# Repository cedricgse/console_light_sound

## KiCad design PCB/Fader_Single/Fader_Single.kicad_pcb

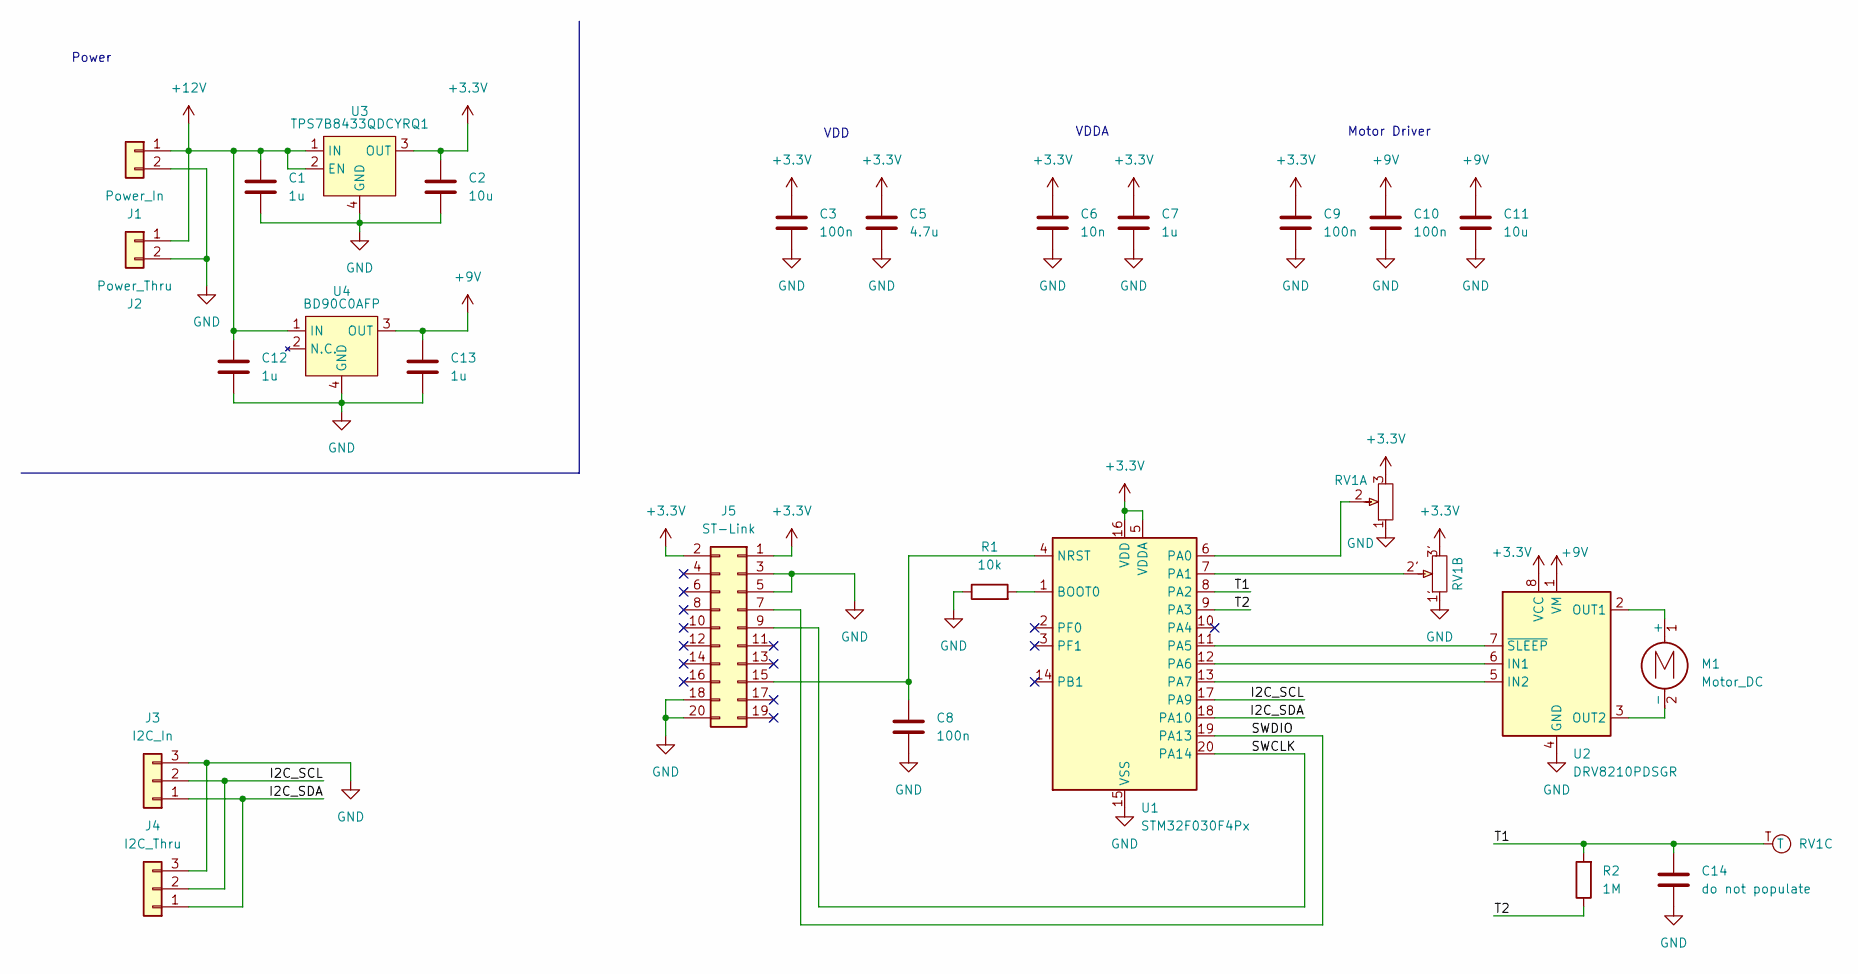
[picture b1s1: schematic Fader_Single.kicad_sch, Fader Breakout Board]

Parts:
C1, C7, C12, C13: 1u; C_0805_2012Metric
C2, C11: 10u; C_0805_2012Metric
C3, C8, C9, C10: 100n; C_0805_2012Metric
C5: 4.7u; C_0805_2012Metric
C6: 10n; C_0805_2012Metric
C14: do not populate; C_0805_2012Metric
J1: Power_In; PinHeader_1x02_P2.54mm_Vertical
J2: Power_Thru; PinHeader_1x02_P2.54mm_Vertical
J3: I2C_In; PinHeader_1x03_P2.54mm_Vertical
J4: I2C_Thru; PinHeader_1x03_P2.54mm_Vertical
J5: ST-Link; PinHeader_2x10_P2.54mm_Vertical
M1: Motor_DC; SolderWire-0.5sqmm_1x02_P4.8mm_D0.9mm_OD2.3mm
R1: 10k; R_0805_2012Metric
R2: 1M; R_0805_2012Metric
RV1: Motorfader
U1: STM32F030F4Px; TSSOP-20_4.4x6.5mm_P0.65mm
U2: DRV8210PDSGR; WSON-8-1EP_2x2mm_P0.5mm_EP0.9x1.6mm_ThermalVias
U3: TPS7B8433QDCYRQ1; SOT-223
U4: BD90C0AFP; TO-252-3_TabPin4

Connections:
+3.3V: C2.1, C3.1, C5.1, C6.1, C7.1, C9.1, J5.1, J5.2, RV1.3, RV1.3', U1.5 (VDDA), U1.16 (VDD), U2.8 (VCC), U3.3 (OUT)
+9V: C10.1, C11.1, C13.1, U2.1 (VM), U4.3 (OUT)
+12V: C1.1, C12.1, J1.1, J2.1, U3.1 (IN), U3.2 (EN), U4.1 (IN)
/I2C_SCL: J3.2, J4.2, U1.17 (PA9)
/I2C_SDA: J3.1, J4.1, U1.18 (PA10)
/SWCLK: J5.9, U1.20 (PA14)
/SWDIO: J5.7, U1.19 (PA13)
/T1: C14.1, R2.2, RV1.T, U1.8 (PA2)
/T2: R2.1, U1.9 (PA3)
GND: C1.2, C2.2, C3.2, C5.2, C6.2, C7.2, C8.2, C9.2, C10.2, C11.2, C12.2, C13.2, C14.2, J1.2, J2.2, J3.3, J4.3, J5.3, J5.5, J5.18, J5.20, R1.1, RV1.1, RV1.1', U1.15 (VSS), U2.4 (GND), U2.9 (GND), U3.4 (GND), U4.4 (GND)
unnamed: C8.1, J5.15, U1.4 (NRST)
unnamed: M1.1 (+), U2.2 (OUT1)
unnamed: M1.2 (-), U2.3 (OUT2)
unnamed: R1.2, U1.1 (BOOT0)
unnamed: RV1.2, U1.6 (PA0)
unnamed: RV1.2', U1.7 (PA1)
unnamed: U1.11 (PA5), U2.7 (~SLEEP)
unnamed: U1.12 (PA6), U2.6 (IN1)
unnamed: U1.13 (PA7), U2.5 (IN2)

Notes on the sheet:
VDDA
Power
Motor Driver
VDD

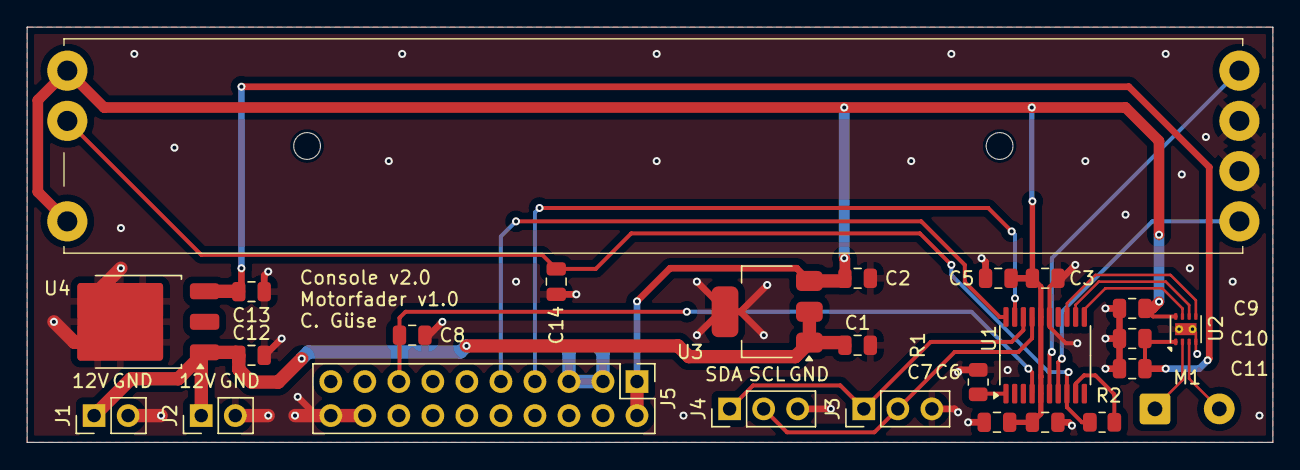
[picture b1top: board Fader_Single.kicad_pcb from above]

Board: 2 copper layers, 93.0 x 31.0 mm, 26 parts (0 on the bottom side), 19 nets.

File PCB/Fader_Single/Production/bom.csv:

Designator,Footprint,Quantity,Value,LCSC Part #
"C1, C12, C13, C7",0805,4,1u,
"C10, C3, C8, C9",0805,4,100n,
"C11, C2",0805,2,10u,
C14,0805,1,do not populate,
C5,0805,1,4.7u,
C6,0805,1,10n,
J1,PinHeader_1x02_P2.54mm_Vertical,1,Power_In,
J2,PinHeader_1x02_P2.54mm_Vertical,1,Power_Thru,
J3,PinHeader_1x03_P2.54mm_Vertical,1,I2C_In,
J4,PinHeader_1x03_P2.54mm_Vertical,1,I2C_Thru,
J5,PinHeader_2x10_P2.54mm_Vertical,1,ST-Link,
M1,SolderWire-0.5sqmm_1x02_P4.8mm_D0.9mm_OD2.3mm,1,Motor_DC,
R1,0805,1,10k,
R2,0805,1,1M,
RV1,Motorfader,1,~,
U1,TSSOP-20_4.4x6.5mm_P0.65mm,1,STM32F030F4Px,
U2,WSON-8-1EP_2x2mm_P0.5mm_EP0.9x1.6mm_ThermalVias,1,DRV8210PDSGR,
U3,SOT-223,1,~,
U4,TO-252-3_TabPin4,1,~,

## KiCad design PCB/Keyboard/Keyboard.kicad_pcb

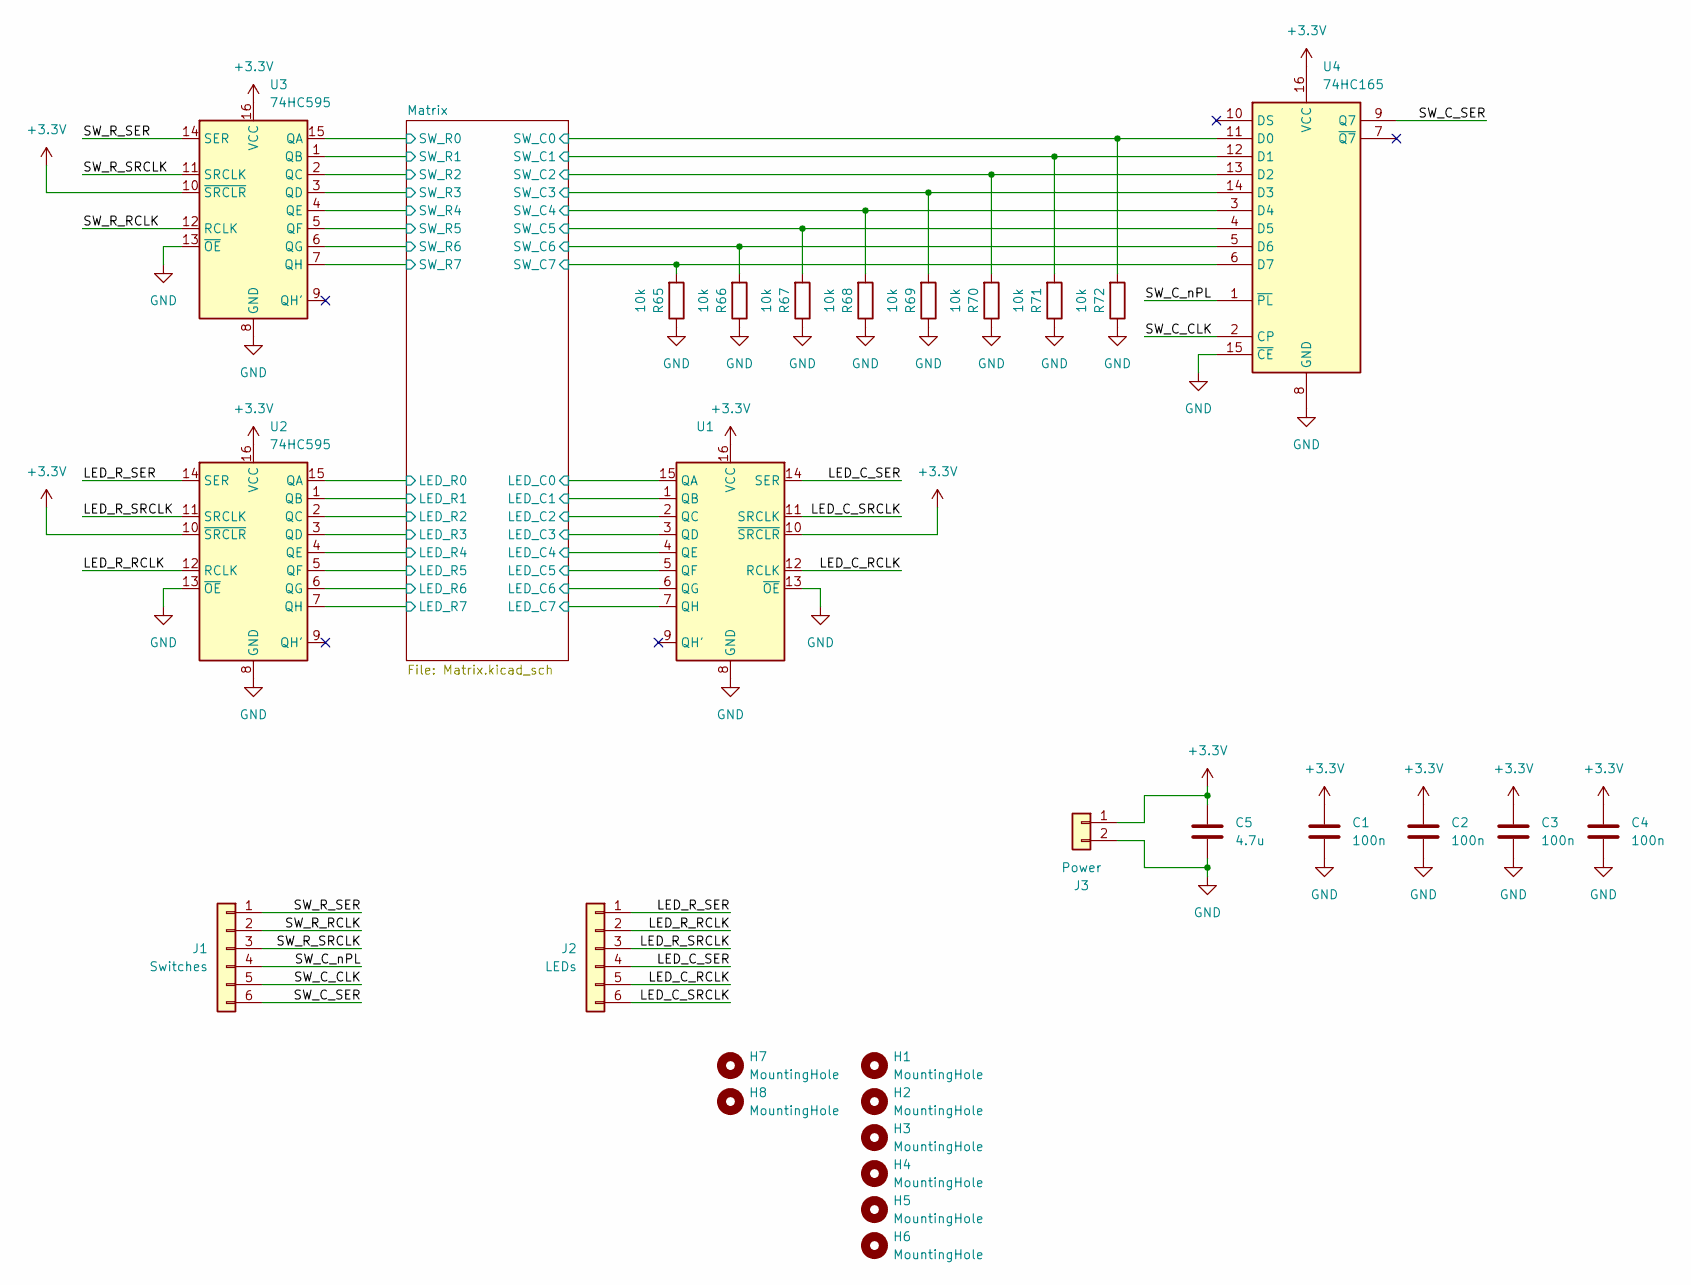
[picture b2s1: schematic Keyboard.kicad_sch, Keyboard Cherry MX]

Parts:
C1, C2, C3, C4: 100n; C_0805_2012Metric
C5: 4.7u; C_0805_2012Metric
H1, H2, H3, H4, H5, H6, H7, H8: MountingHole; MountingHole_3.2mm_M3
J1: Switches; PinHeader_1x06_P2.54mm_Vertical
J2: LEDs; PinHeader_1x06_P2.54mm_Vertical
J3: Power; PinHeader_1x02_P2.54mm_Vertical
R65, R66, R67, R68, R69, R70, R71, R72: 10k; R_0805_2012Metric
U1, U2, U3: 74HC595; SO-16_3.9x9.9mm_P1.27mm
U4: 74HC165; SO-16_3.9x9.9mm_P1.27mm

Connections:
+3.3V: C1.1, C2.1, C3.1, C4.1, C5.1, J3.1, U1.10 (~SRCLR), U1.16 (VCC), U2.10 (~SRCLR), U2.16 (VCC), U3.10 (~SRCLR), U3.16 (VCC), U4.16 (VCC)
/LED_C_RCLK: J2.5, U1.12 (RCLK)
/LED_C_SER: J2.4, U1.14 (SER)
/LED_C_SRCLK: J2.6, U1.11 (SRCLK)
/LED_R_RCLK: J2.2, U2.12 (RCLK)
/LED_R_SER: J2.1, U2.14 (SER)
/LED_R_SRCLK: J2.3, U2.11 (SRCLK)
/Matrix/LED_C0: U1.15 (QA); also elsewhere on the board
/Matrix/LED_C1: U1.1 (QB); also elsewhere on the board
/Matrix/LED_C2: U1.2 (QC); also elsewhere on the board
/Matrix/LED_C3: U1.3 (QD); also elsewhere on the board
/Matrix/LED_C4: U1.4 (QE); also elsewhere on the board
/Matrix/LED_C5: U1.5 (QF); also elsewhere on the board
/Matrix/LED_C6: U1.6 (QG); also elsewhere on the board
/Matrix/LED_C7: U1.7 (QH); also elsewhere on the board
/Matrix/LED_R0: U2.15 (QA); also elsewhere on the board
/Matrix/LED_R1: U2.1 (QB); also elsewhere on the board
/Matrix/LED_R2: U2.2 (QC); also elsewhere on the board
/Matrix/LED_R3: U2.3 (QD); also elsewhere on the board
/Matrix/LED_R4: U2.4 (QE); also elsewhere on the board
/Matrix/LED_R5: U2.5 (QF); also elsewhere on the board
/Matrix/LED_R6: U2.6 (QG); also elsewhere on the board
/Matrix/LED_R7: U2.7 (QH); also elsewhere on the board
/Matrix/SW_C0: R72.2, U4.11 (D0); also elsewhere on the board
/Matrix/SW_C1: R71.2, U4.12 (D1); also elsewhere on the board
/Matrix/SW_C2: R70.2, U4.13 (D2); also elsewhere on the board
/Matrix/SW_C3: R69.2, U4.14 (D3); also elsewhere on the board
/Matrix/SW_C4: R68.2, U4.3 (D4); also elsewhere on the board
/Matrix/SW_C5: R67.2, U4.4 (D5); also elsewhere on the board
/Matrix/SW_C6: R66.2, U4.5 (D6); also elsewhere on the board
/Matrix/SW_C7: R65.2, U4.6 (D7); also elsewhere on the board
/Matrix/SW_R0: U3.15 (QA); also elsewhere on the board
/Matrix/SW_R1: U3.1 (QB); also elsewhere on the board
/Matrix/SW_R2: U3.2 (QC); also elsewhere on the board
/Matrix/SW_R3: U3.3 (QD); also elsewhere on the board
/Matrix/SW_R4: U3.4 (QE); also elsewhere on the board
/Matrix/SW_R5: U3.5 (QF); also elsewhere on the board
/Matrix/SW_R6: U3.6 (QG); also elsewhere on the board
/Matrix/SW_R7: U3.7 (QH); also elsewhere on the board
/SW_C_CLK: J1.5, U4.2 (CP)
/SW_C_SER: J1.6, U4.9 (Q7)
/SW_C_nPL: J1.4, U4.1 (~PL)
/SW_R_RCLK: J1.2, U3.12 (RCLK)
/SW_R_SER: J1.1, U3.14 (SER)
/SW_R_SRCLK: J1.3, U3.11 (SRCLK)
GND: C1.2, C2.2, C3.2, C4.2, C5.2, J3.2, R65.1, R66.1, R67.1, R68.1, R69.1, R70.1, R71.1, R72.1, U1.8 (GND), U1.13 (~OE), U2.8 (GND), U2.13 (~OE), U3.8 (GND), U3.13 (~OE), U4.8 (GND), U4.15 (~CE)

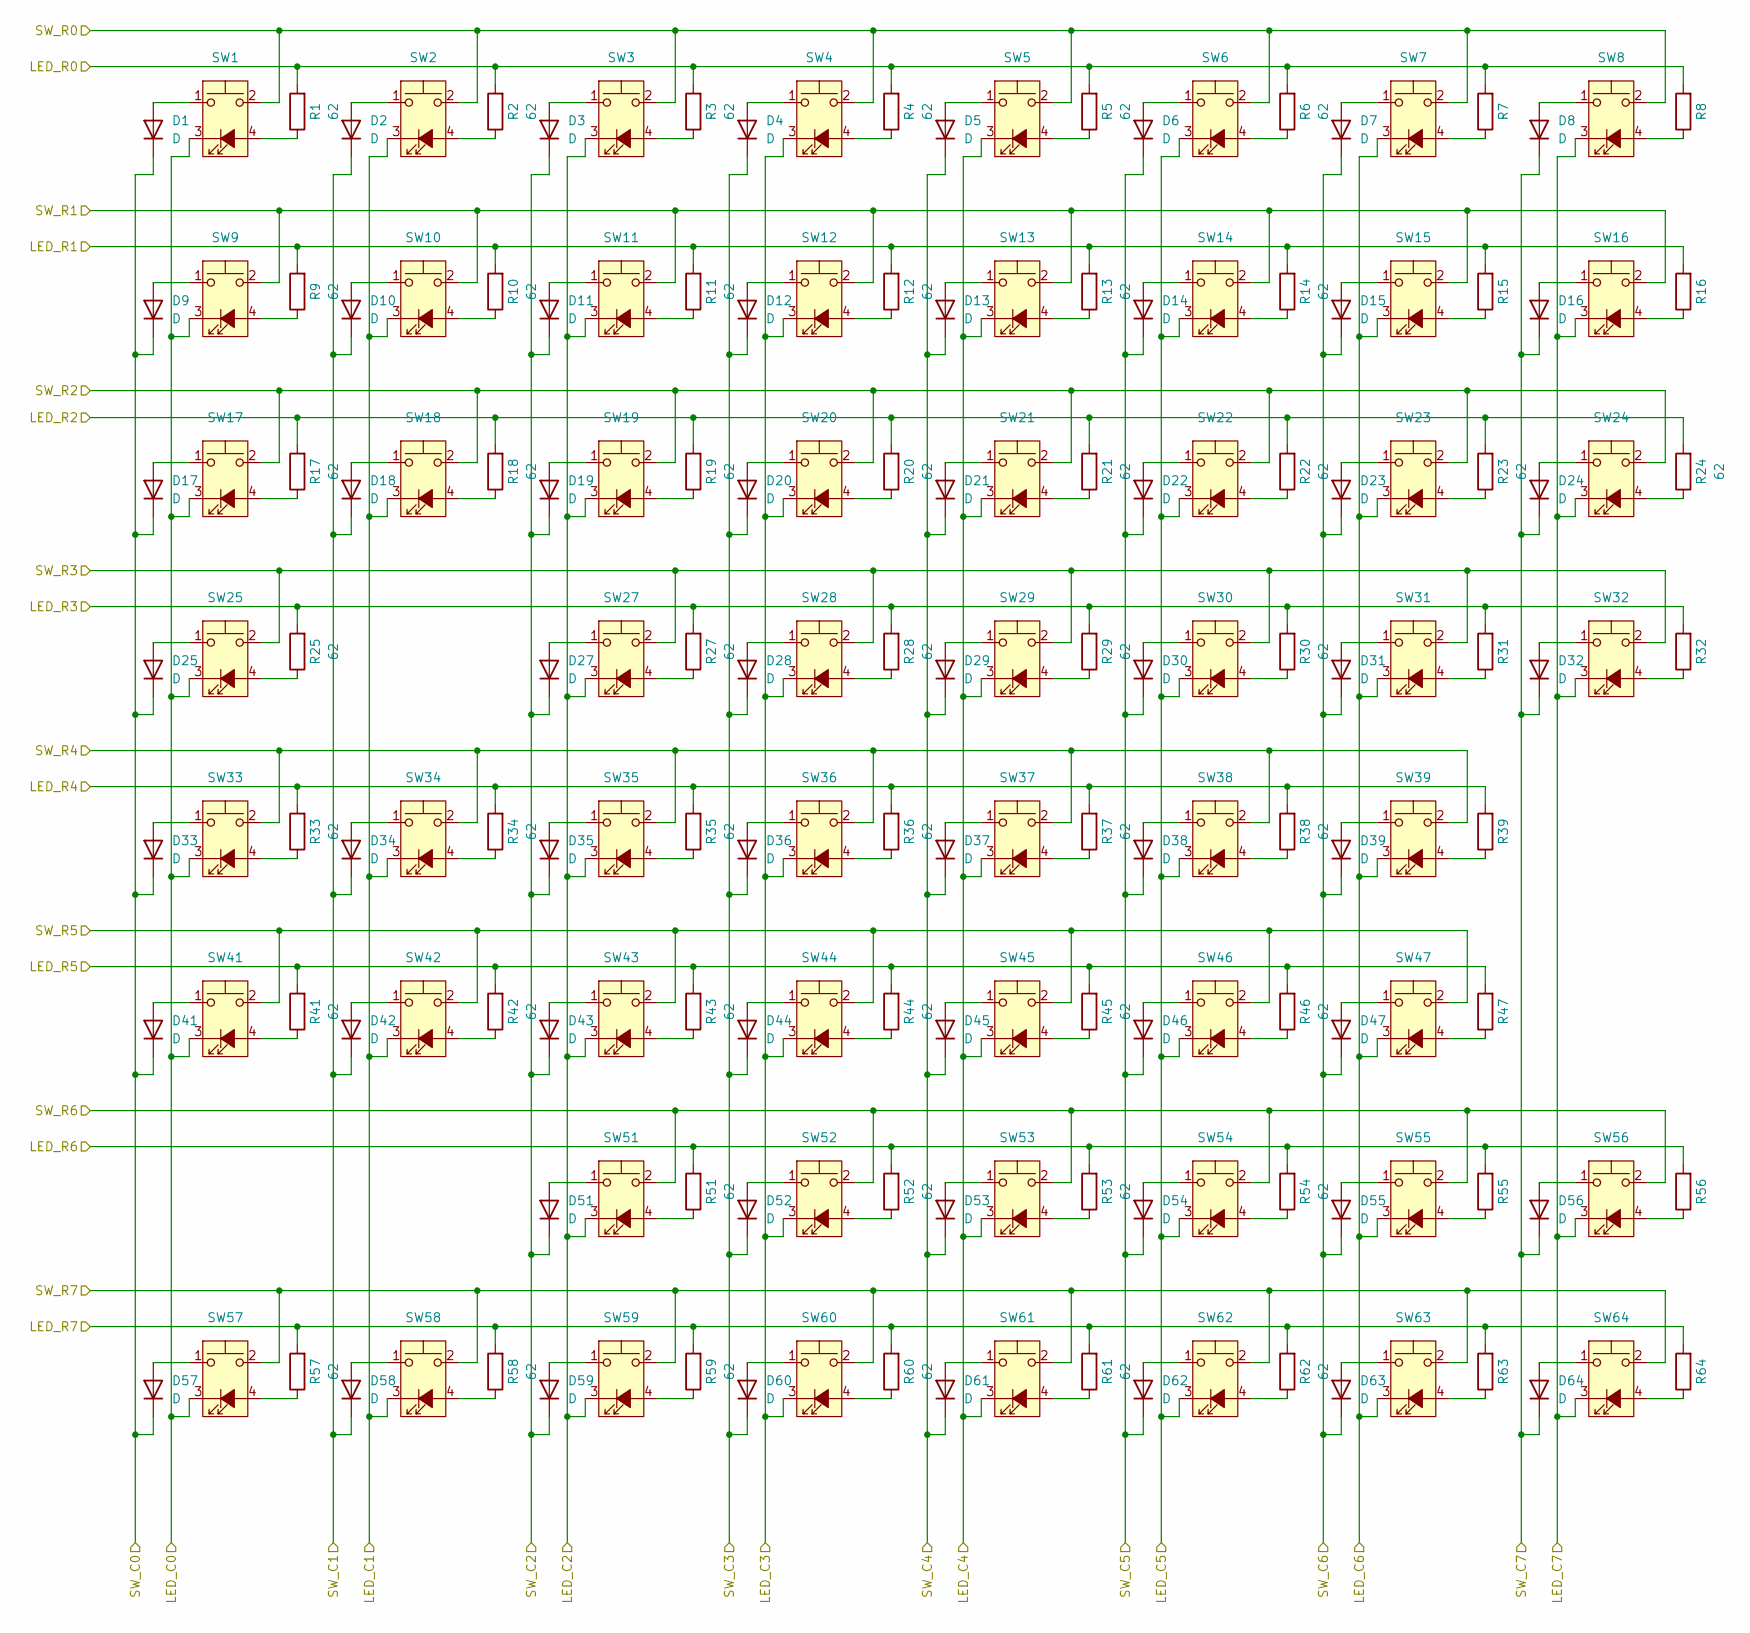
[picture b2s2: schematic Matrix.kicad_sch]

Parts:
D1, D2, D3, D4, D5, D6, D7, D8, D9, D10, D11, D12, D13, D14, D15, D16, D17, D18, D19, D20, D21, D22, D23, D24, D25, D27, D28, D29, D30, D31, D32, D33, D34, D35, D36, D37, D38, D39, D41, D42, D43, D44, D45, D46, D47, D51, D52, D53, D54, D55, D56, D57, D58, D59, D60, D61, D62, D63, D64: D; D_0805_2012Metric
R1, R2, R3, R4, R5, R6, R7, R8, R9, R10, R11, R12, R13, R14, R15, R16, R17, R18, R19, R20, R21, R22, R23, R24, R25, R27, R28, R29, R30, R31, R32, R33, R34, R35, R36, R37, R38, R39, R41, R42, R43, R44, R45, R46, R47, R51, R52, R53, R54, R55, R56, R57, R58, R59, R60, R61, R62, R63, R64: 62; R_0805_2012Metric
SW1, SW2, SW3, SW4, SW5, SW6, SW7, SW8, SW9, SW10, SW11, SW12, SW13, SW14, SW15, SW16, SW17, SW18, SW19, SW20, SW21, SW22, SW23, SW24, SW25, SW27, SW28, SW29, SW30, SW31, SW32, SW33, SW34, SW35, SW36, SW37, SW38, SW39, SW41, SW42, SW43, SW44, SW45, SW46, SW47, SW51, SW52, SW53, SW54, SW55, SW56, SW57, SW58, SW59, SW60, SW61, SW62, SW63, SW64: Cherry MX

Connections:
/Matrix/LED_C0: SW1.3, SW9.3, SW17.3, SW25.3, SW33.3, SW41.3, SW57.3; also elsewhere on the board
/Matrix/LED_C1: SW2.3, SW10.3, SW18.3, SW34.3, SW42.3, SW58.3; also elsewhere on the board
/Matrix/LED_C2: SW3.3, SW11.3, SW19.3, SW27.3, SW35.3, SW43.3, SW51.3, SW59.3; also elsewhere on the board
/Matrix/LED_C3: SW4.3, SW12.3, SW20.3, SW28.3, SW36.3, SW44.3, SW52.3, SW60.3; also elsewhere on the board
/Matrix/LED_C4: SW5.3, SW13.3, SW21.3, SW29.3, SW37.3, SW45.3, SW53.3, SW61.3; also elsewhere on the board
/Matrix/LED_C5: SW6.3, SW14.3, SW22.3, SW30.3, SW38.3, SW46.3, SW54.3, SW62.3; also elsewhere on the board
/Matrix/LED_C6: SW7.3, SW15.3, SW23.3, SW31.3, SW39.3, SW47.3, SW55.3, SW63.3; also elsewhere on the board
/Matrix/LED_C7: SW8.3, SW16.3, SW24.3, SW32.3, SW56.3, SW64.3; also elsewhere on the board
/Matrix/LED_R0: R1.2, R2.2, R3.2, R4.2, R5.2, R6.2, R7.2, R8.2; also elsewhere on the board
/Matrix/LED_R1: R9.2, R10.2, R11.2, R12.2, R13.2, R14.2, R15.2, R16.2; also elsewhere on the board
/Matrix/LED_R2: R17.2, R18.2, R19.2, R20.2, R21.2, R22.2, R23.2, R24.2; also elsewhere on the board
/Matrix/LED_R3: R25.2, R27.2, R28.2, R29.2, R30.2, R31.2, R32.2; also elsewhere on the board
/Matrix/LED_R4: R33.2, R34.2, R35.2, R36.2, R37.2, R38.2, R39.2; also elsewhere on the board
/Matrix/LED_R5: R41.2, R42.2, R43.2, R44.2, R45.2, R46.2, R47.2; also elsewhere on the board
/Matrix/LED_R6: R51.2, R52.2, R53.2, R54.2, R55.2, R56.2; also elsewhere on the board
/Matrix/LED_R7: R57.2, R58.2, R59.2, R60.2, R61.2, R62.2, R63.2, R64.2; also elsewhere on the board
/Matrix/SW_C0: D1.1 (K), D9.1 (K), D17.1 (K), D25.1 (K), D33.1 (K), D41.1 (K), D57.1 (K); also elsewhere on the board
/Matrix/SW_C1: D2.1 (K), D10.1 (K), D18.1 (K), D34.1 (K), D42.1 (K), D58.1 (K); also elsewhere on the board
/Matrix/SW_C2: D3.1 (K), D11.1 (K), D19.1 (K), D27.1 (K), D35.1 (K), D43.1 (K), D51.1 (K), D59.1 (K); also elsewhere on the board
/Matrix/SW_C3: D4.1 (K), D12.1 (K), D20.1 (K), D28.1 (K), D36.1 (K), D44.1 (K), D52.1 (K), D60.1 (K); also elsewhere on the board
/Matrix/SW_C4: D5.1 (K), D13.1 (K), D21.1 (K), D29.1 (K), D37.1 (K), D45.1 (K), D53.1 (K), D61.1 (K); also elsewhere on the board
/Matrix/SW_C5: D6.1 (K), D14.1 (K), D22.1 (K), D30.1 (K), D38.1 (K), D46.1 (K), D54.1 (K), D62.1 (K); also elsewhere on the board
/Matrix/SW_C6: D7.1 (K), D15.1 (K), D23.1 (K), D31.1 (K), D39.1 (K), D47.1 (K), D55.1 (K), D63.1 (K); also elsewhere on the board
/Matrix/SW_C7: D8.1 (K), D16.1 (K), D24.1 (K), D32.1 (K), D56.1 (K), D64.1 (K); also elsewhere on the board
/Matrix/SW_R0: SW1.2, SW2.2, SW3.2, SW4.2, SW5.2, SW6.2, SW7.2, SW8.2; also elsewhere on the board
/Matrix/SW_R1: SW9.2, SW10.2, SW11.2, SW12.2, SW13.2, SW14.2, SW15.2, SW16.2; also elsewhere on the board
/Matrix/SW_R2: SW17.2, SW18.2, SW19.2, SW20.2, SW21.2, SW22.2, SW23.2, SW24.2; also elsewhere on the board
/Matrix/SW_R3: SW25.2, SW27.2, SW28.2, SW29.2, SW30.2, SW31.2, SW32.2; also elsewhere on the board
/Matrix/SW_R4: SW33.2, SW34.2, SW35.2, SW36.2, SW37.2, SW38.2, SW39.2; also elsewhere on the board
/Matrix/SW_R5: SW41.2, SW42.2, SW43.2, SW44.2, SW45.2, SW46.2, SW47.2; also elsewhere on the board
/Matrix/SW_R6: SW51.2, SW52.2, SW53.2, SW54.2, SW55.2, SW56.2; also elsewhere on the board
/Matrix/SW_R7: SW57.2, SW58.2, SW59.2, SW60.2, SW61.2, SW62.2, SW63.2, SW64.2; also elsewhere on the board
unnamed: D1.2 (A), SW1.1
unnamed: D2.2 (A), SW2.1
unnamed: D3.2 (A), SW3.1
unnamed: D4.2 (A), SW4.1
unnamed: D5.2 (A), SW5.1
unnamed: D6.2 (A), SW6.1
unnamed: D7.2 (A), SW7.1
unnamed: D8.2 (A), SW8.1
unnamed: D9.2 (A), SW9.1
unnamed: D10.2 (A), SW10.1
unnamed: D11.2 (A), SW11.1
unnamed: D12.2 (A), SW12.1
unnamed: D13.2 (A), SW13.1
unnamed: D14.2 (A), SW14.1
unnamed: D15.2 (A), SW15.1
unnamed: D16.2 (A), SW16.1
unnamed: D17.2 (A), SW17.1
unnamed: D18.2 (A), SW18.1
unnamed: D19.2 (A), SW19.1
unnamed: D20.2 (A), SW20.1
unnamed: D21.2 (A), SW21.1
unnamed: D22.2 (A), SW22.1
unnamed: D23.2 (A), SW23.1
unnamed: D24.2 (A), SW24.1
unnamed: D25.2 (A), SW25.1
unnamed: D27.2 (A), SW27.1
unnamed: D28.2 (A), SW28.1
unnamed: D29.2 (A), SW29.1
unnamed: D30.2 (A), SW30.1
unnamed: D31.2 (A), SW31.1
unnamed: D32.2 (A), SW32.1
unnamed: D33.2 (A), SW33.1
unnamed: D34.2 (A), SW34.1
unnamed: D35.2 (A), SW35.1
unnamed: D36.2 (A), SW36.1
unnamed: D37.2 (A), SW37.1
unnamed: D38.2 (A), SW38.1
unnamed: D39.2 (A), SW39.1
unnamed: D41.2 (A), SW41.1
unnamed: D42.2 (A), SW42.1
unnamed: D43.2 (A), SW43.1
unnamed: D44.2 (A), SW44.1
unnamed: D45.2 (A), SW45.1
unnamed: D46.2 (A), SW46.1
unnamed: D47.2 (A), SW47.1
unnamed: D51.2 (A), SW51.1
unnamed: D52.2 (A), SW52.1
unnamed: D53.2 (A), SW53.1
unnamed: D54.2 (A), SW54.1
unnamed: D55.2 (A), SW55.1
unnamed: D56.2 (A), SW56.1
unnamed: D57.2 (A), SW57.1
unnamed: D58.2 (A), SW58.1
unnamed: D59.2 (A), SW59.1
unnamed: D60.2 (A), SW60.1
unnamed: D61.2 (A), SW61.1
unnamed: D62.2 (A), SW62.1
unnamed: D63.2 (A), SW63.1
unnamed: D64.2 (A), SW64.1
unnamed: R1.1, SW1.4
unnamed: R2.1, SW2.4
unnamed: R3.1, SW3.4
unnamed: R4.1, SW4.4
unnamed: R5.1, SW5.4
unnamed: R6.1, SW6.4
unnamed: R7.1, SW7.4
unnamed: R8.1, SW8.4
unnamed: R9.1, SW9.4
unnamed: R10.1, SW10.4
unnamed: R11.1, SW11.4
unnamed: R12.1, SW12.4
unnamed: R13.1, SW13.4
unnamed: R14.1, SW14.4
unnamed: R15.1, SW15.4
unnamed: R16.1, SW16.4
unnamed: R17.1, SW17.4
unnamed: R18.1, SW18.4
unnamed: R19.1, SW19.4
unnamed: R20.1, SW20.4
unnamed: R21.1, SW21.4
unnamed: R22.1, SW22.4
unnamed: R23.1, SW23.4
unnamed: R24.1, SW24.4
unnamed: R25.1, SW25.4
unnamed: R27.1, SW27.4
unnamed: R28.1, SW28.4
unnamed: R29.1, SW29.4
unnamed: R30.1, SW30.4
unnamed: R31.1, SW31.4
unnamed: R32.1, SW32.4
unnamed: R33.1, SW33.4
unnamed: R34.1, SW34.4
unnamed: R35.1, SW35.4
unnamed: R36.1, SW36.4
unnamed: R37.1, SW37.4
unnamed: R38.1, SW38.4
unnamed: R39.1, SW39.4
unnamed: R41.1, SW41.4
unnamed: R42.1, SW42.4
unnamed: R43.1, SW43.4
unnamed: R44.1, SW44.4
unnamed: R45.1, SW45.4
unnamed: R46.1, SW46.4
unnamed: R47.1, SW47.4
unnamed: R51.1, SW51.4
unnamed: R52.1, SW52.4
unnamed: R53.1, SW53.4
unnamed: R54.1, SW54.4
unnamed: R55.1, SW55.4
unnamed: R56.1, SW56.4
unnamed: R57.1, SW57.4
unnamed: R58.1, SW58.4
unnamed: R59.1, SW59.4
unnamed: R60.1, SW60.4
unnamed: R61.1, SW61.4
unnamed: R62.1, SW62.4
unnamed: R63.1, SW63.4
unnamed: R64.1, SW64.4

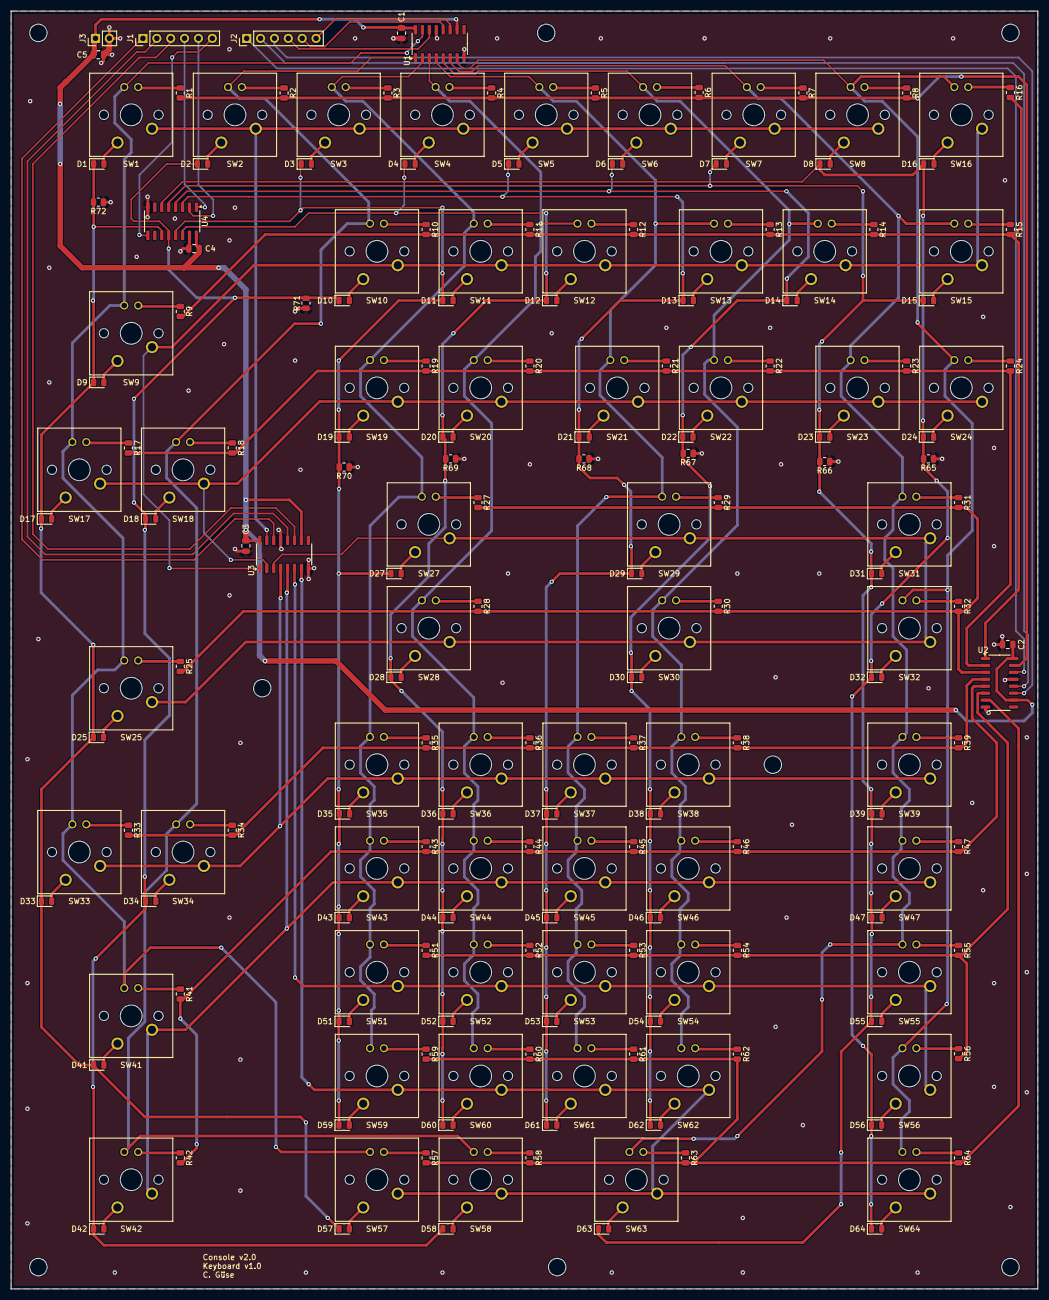
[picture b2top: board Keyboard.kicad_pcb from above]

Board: 2 copper layers, 188.0 x 234.0 mm, 205 parts (0 on the bottom side), 164 nets.

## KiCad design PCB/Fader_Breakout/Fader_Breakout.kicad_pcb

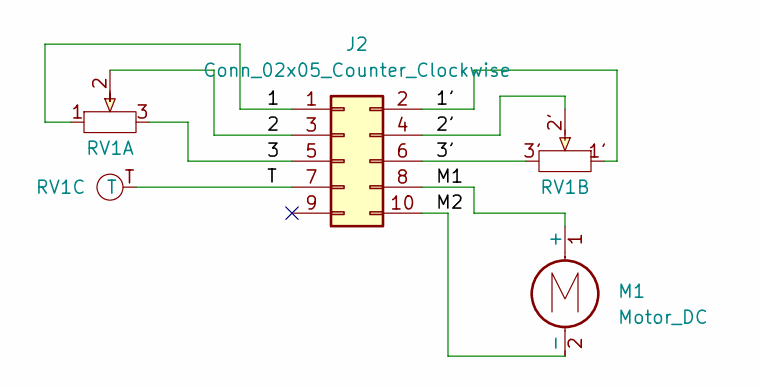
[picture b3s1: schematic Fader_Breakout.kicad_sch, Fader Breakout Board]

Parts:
J2: Conn_02x05_Counter_Clockwise; PinHeader_2x05_P2.54mm_Vertical
M1: Motor_DC; SolderWire-0.5sqmm_1x02_P4.8mm_D0.9mm_OD2.3mm
RV1: Motorfader

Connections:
/1: J2.1, RV1.1
/1': J2.2, RV1.1'
/2: J2.3, RV1.2
/2': J2.4, RV1.2'
/3: J2.5, RV1.3
/3': J2.6, RV1.3'
/M1: J2.8, M1.1 (+)
/M2: J2.10, M1.2 (-)
/T: J2.7, RV1.T

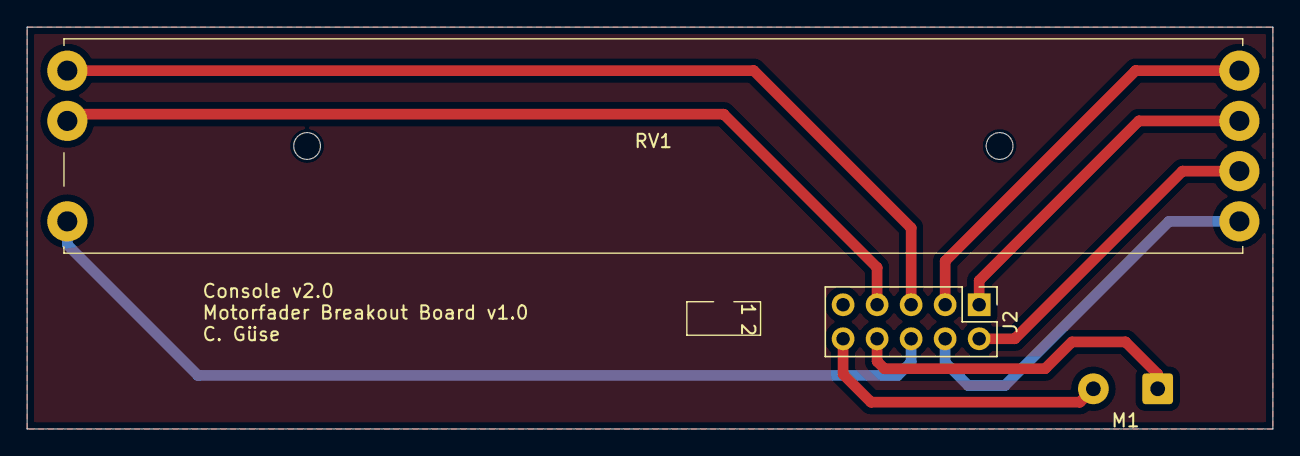
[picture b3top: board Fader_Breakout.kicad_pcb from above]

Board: 2 copper layers, 93.0 x 30.0 mm, 3 parts (0 on the bottom side), 9 nets.

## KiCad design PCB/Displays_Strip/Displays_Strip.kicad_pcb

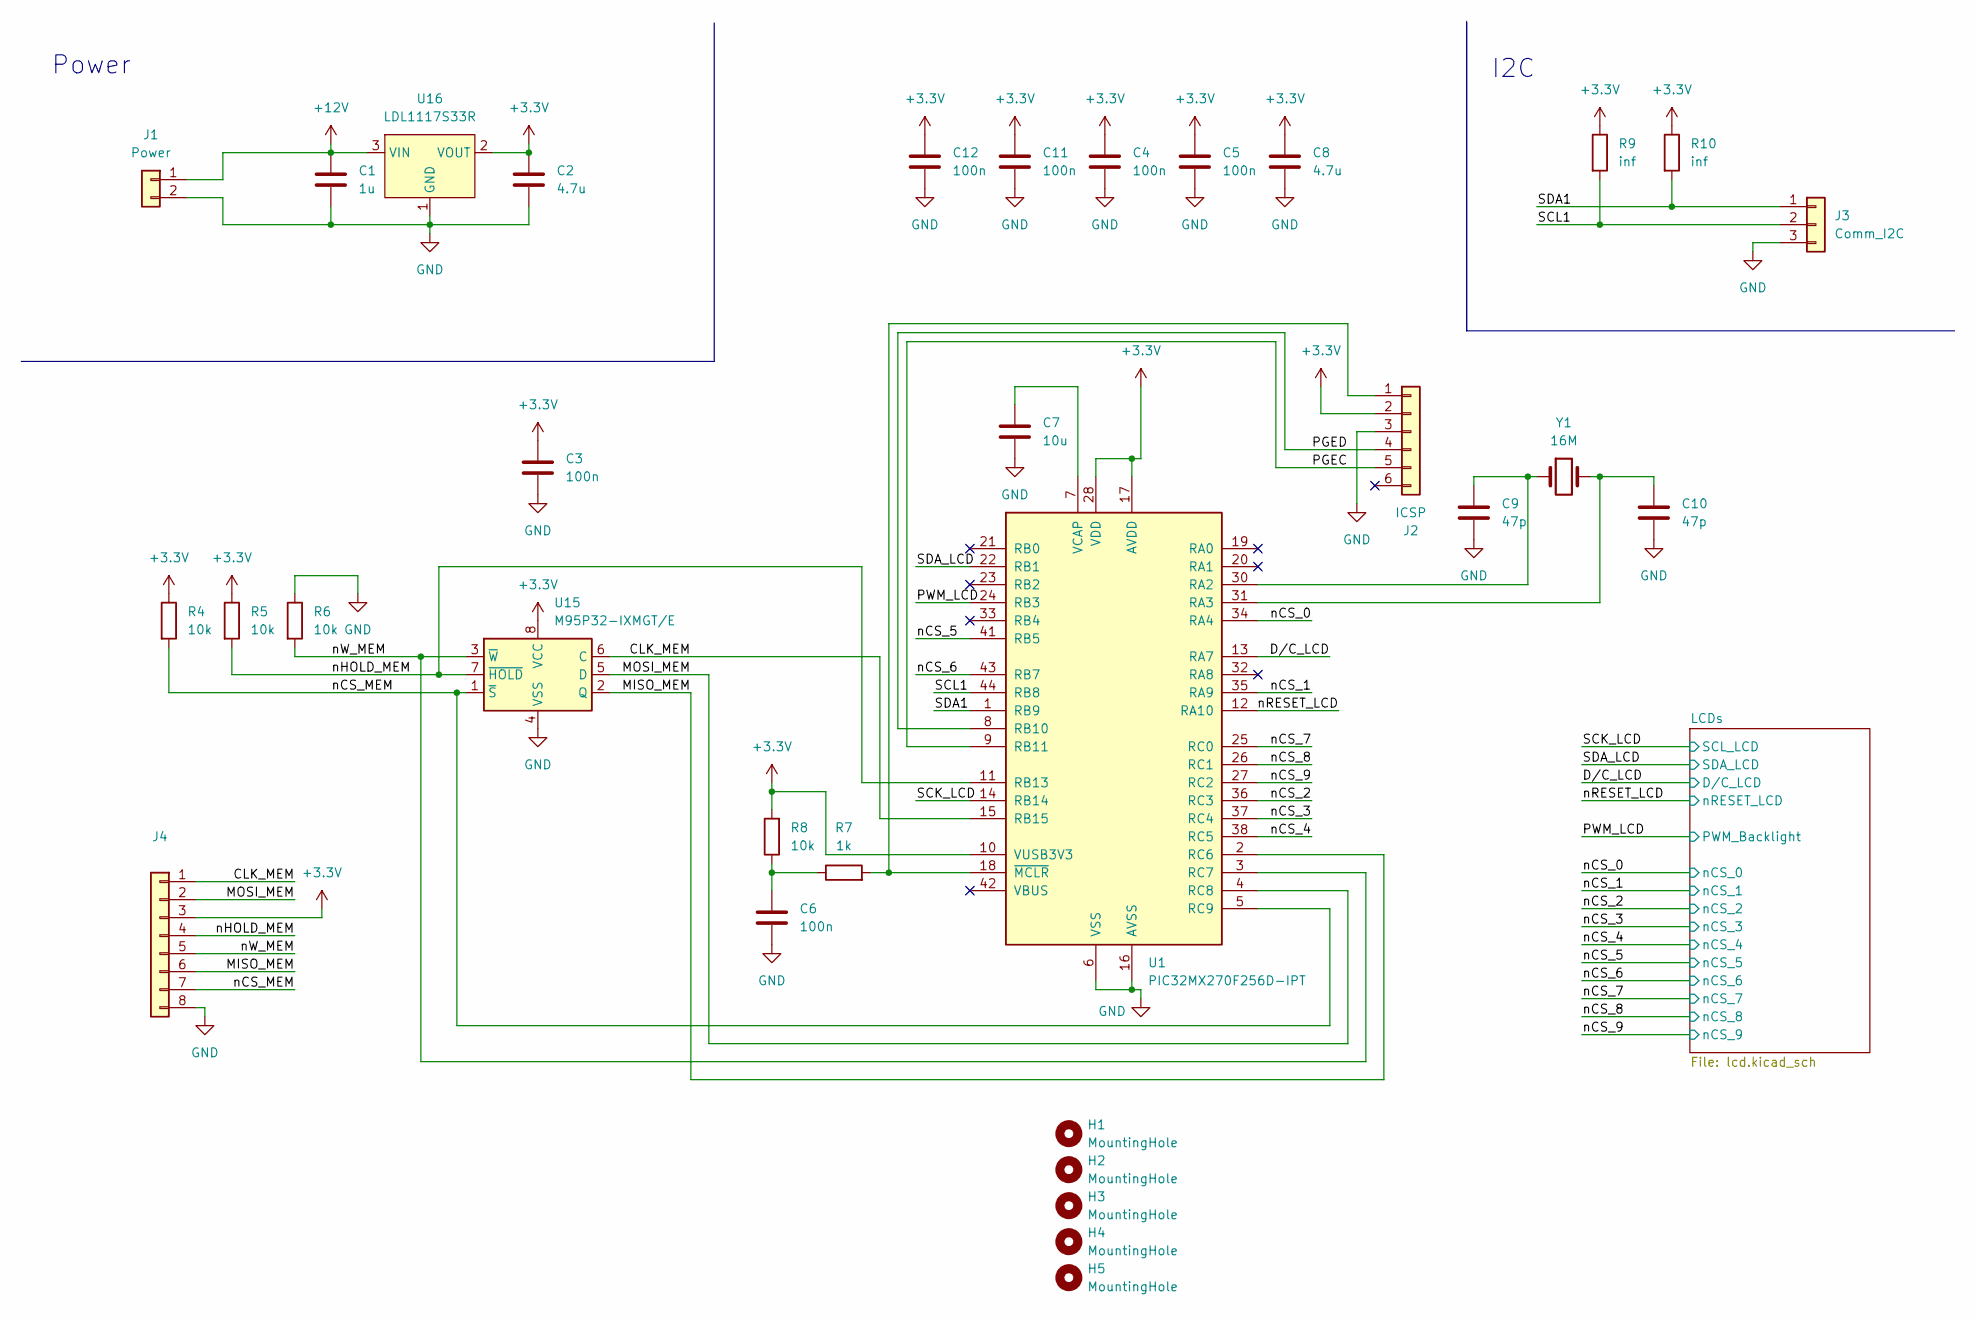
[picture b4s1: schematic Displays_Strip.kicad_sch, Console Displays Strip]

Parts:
C1: 1u; C_0805_2012Metric
C2, C8: 4.7u; C_0805_2012Metric
C3, C4, C5, C6, C11, C12: 100n; C_0805_2012Metric
C7: 10u; C_0805_2012Metric
C9, C10: 47p; C_0805_2012Metric
H1, H2, H3, H4, H5: MountingHole; MountingHole_3.2mm_M3
J1: Power; PinHeader_1x02_P2.54mm_Vertical
J2: ICSP; PinHeader_1x06_P2.54mm_Vertical
J3: Comm_I2C; PinHeader_1x03_P2.54mm_Vertical
J4: EEPROM_Prog; PinHeader_1x08_P2.54mm_Vertical
R4, R5, R6, R8: 10k; R_0805_2012Metric
R7: 1k; R_0805_2012Metric
R9, R10: inf; R_0805_2012Metric
U1: PIC32MX270F256D-IPT; TQFP-44_10x10mm_P0.8mm
U15: M95P32-IXMGT/E; SOIC-8_3.9x4.9mm_P1.27mm
U16: LDL1117S33R; SOT-223-3_TabPin2
Y1: 16M; Crystal_HC49-U_Vertical

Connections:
+3.3V: C2.1, C3.1, C4.1, C5.1, C8.1, C11.1, C12.1, J2.2, J4.3, R4.1, R5.1, R8.2, R9.1, R10.1, U1.10 (VUSB3V3), U1.17 (AVDD), U1.28 (VDD), U1.40 (VDD), U15.8 (VCC), U16.2 (VOUT); also elsewhere on the board
+12V: C1.1, J1.1, U16.3 (VIN)
/CLK_MEM: J4.1, U1.15 (RB15), U15.6 (C)
/D/C_LCD: U1.13 (RA7); also elsewhere on the board
/MISO_MEM: J4.6, U1.2 (RC6), U15.2 (Q)
/MOSI_MEM: J4.2, U1.4 (RC8), U15.5 (D)
/PGEC: J2.5, U1.9 (RB11)
/PGED: J2.4, U1.8 (RB10)
/PWM_LCD: U1.24 (RB3); also elsewhere on the board
/SCK_LCD: U1.14 (RB14); also elsewhere on the board
/SCL1: J3.2, R9.2, U1.44 (RB8)
/SDA1: J3.1, R10.2, U1.1 (RB9)
/SDA_LCD: U1.22 (RB1); also elsewhere on the board
/nCS_0: U1.34 (RA4); also elsewhere on the board
/nCS_1: U1.35 (RA9); also elsewhere on the board
/nCS_2: U1.36 (RC3); also elsewhere on the board
/nCS_3: U1.37 (RC4); also elsewhere on the board
/nCS_4: U1.38 (RC5); also elsewhere on the board
/nCS_5: U1.41 (RB5); also elsewhere on the board
/nCS_6: U1.43 (RB7); also elsewhere on the board
/nCS_7: U1.25 (RC0); also elsewhere on the board
/nCS_8: U1.26 (RC1); also elsewhere on the board
/nCS_9: U1.27 (RC2); also elsewhere on the board
/nCS_MEM: J4.7, R4.2, U1.5 (RC9), U15.1 (~S)
/nHOLD_MEM: J4.4, R5.2, U1.11 (RB13), U15.7 (~HOLD)
/nRESET_LCD: U1.12 (RA10); also elsewhere on the board
/nW_MEM: J4.5, R6.2, U1.3 (RC7), U15.3 (~W)
GND: C1.2, C2.2, C3.2, C4.2, C5.2, C6.2, C7.2, C8.2, C9.2, C10.2, C11.2, C12.2, J1.2, J2.3, J3.3, J4.8, R6.1, U1.6 (VSS), U1.16 (AVSS), U1.29 (VSS), U1.39 (VSS), U15.4 (VSS), U16.1 (GND); also elsewhere on the board
unnamed: C6.1, R7.1, R8.1
unnamed: J2.1, R7.2, U1.18 (~MCLR)
unnamed: C9.1, U1.30 (RA2), Y1.1
unnamed: C10.1, U1.31 (RA3), Y1.2
unnamed: C7.1, U1.7 (VCAP)

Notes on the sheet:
I2C
Power
